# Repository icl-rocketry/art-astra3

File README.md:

# art-astra3
A repository for the third member in ART's ASTRA family

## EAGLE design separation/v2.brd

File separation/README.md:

# Separation

Hardware and software for a custom separation project

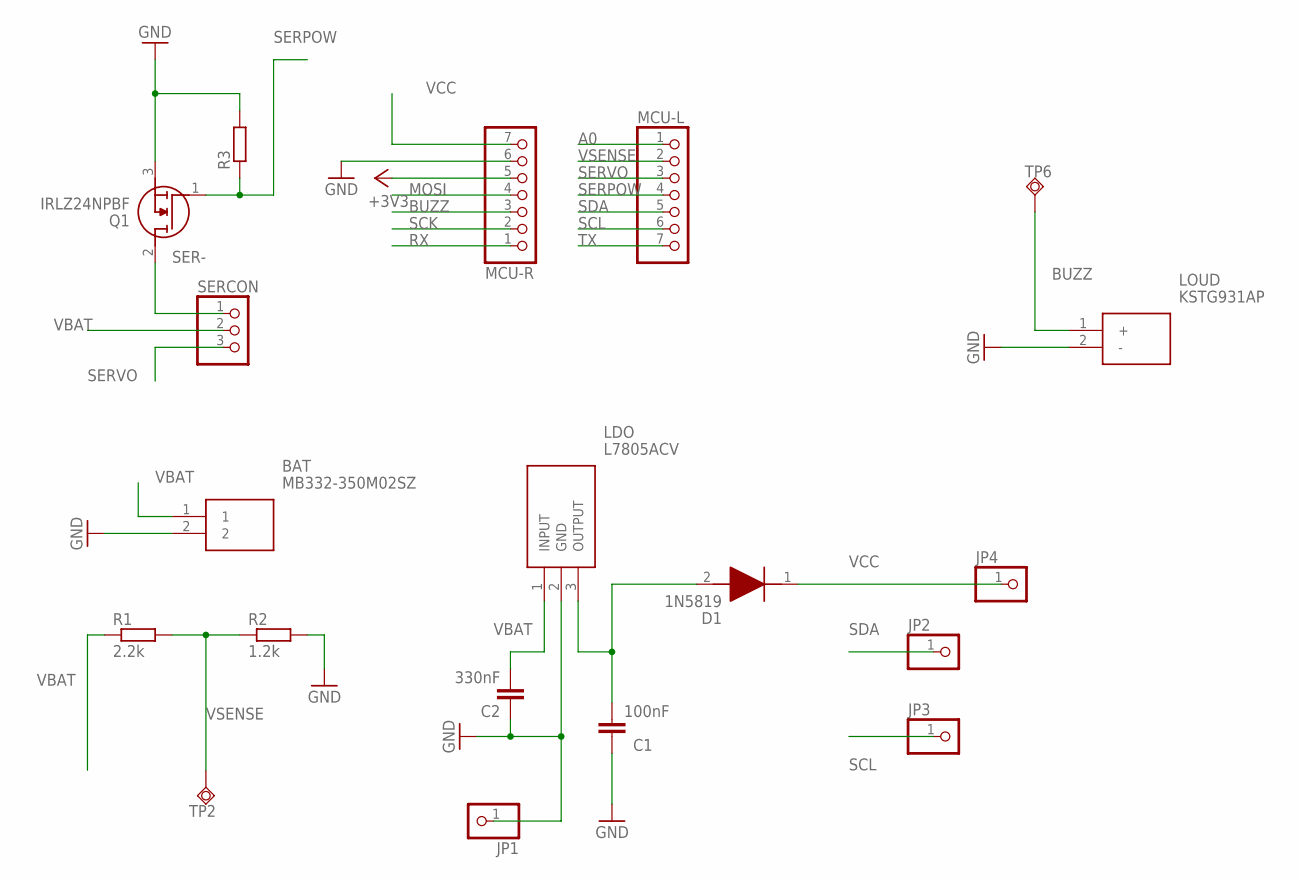
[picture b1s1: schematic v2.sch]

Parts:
BAT: MB332-350M02SZ; MB332350M02SZ
C1: 100nF; C025-024X044
C2: 330nF; C025-024X044
D1: 1N5819; DIOAD1414W86L464D238
JP1, JP2, JP3, JP4: PINHD-1X1; 1X01
LDO: L7805ACV; TO255P460X1020X2008-3P
LOUD: KSTG931AP; CAPPRD400W70D900H500
MCU-L: HEADER-1X7; 1X07_OVAL
MCU-R: HEADER-1X7; 1X07_OVAL
Q1: IRLZ24NPBF; TO254P469X1042X1967-3P
R1: 2.2k; 0204V
R2: 1.2k; 0204V
R3: R-EU_0204/2V; 0204V
SERCON: PINHD-1X3; 1X03
TP2, TP6: TPSQB2,54; B2,54

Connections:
+3V3: MCU-R.5
A0: MCU-L.1
BUZZ: LOUD.1 (+), MCU-R.3, TP6.TP
GND: BAT.2, C1.1, C2.1, JP1.1, LDO.2 (GND), LOUD.2 (-), MCU-R.6, Q1.3 (S), R2.2, R3.2
MOSI: MCU-R.4
RX: MCU-R.1
SCK: MCU-R.2
SCL: JP3.1, MCU-L.6
SDA: JP2.1, MCU-L.5
SER-: Q1.2 (D), SERCON.1
SERPOW: MCU-L.4, Q1.1 (G), R3.1
SERVO: MCU-L.3, SERCON.3
TX: MCU-L.7
VBAT: BAT.1, C2.2, LDO.1 (INPUT), R1.1, SERCON.2
VCC: D1.1 (K), JP4.1, MCU-R.7
VOUT: C1.2, D1.2 (A), LDO.3 (OUTPUT)
VSENSE: MCU-L.2, R1.2, R2.1, TP2.TP

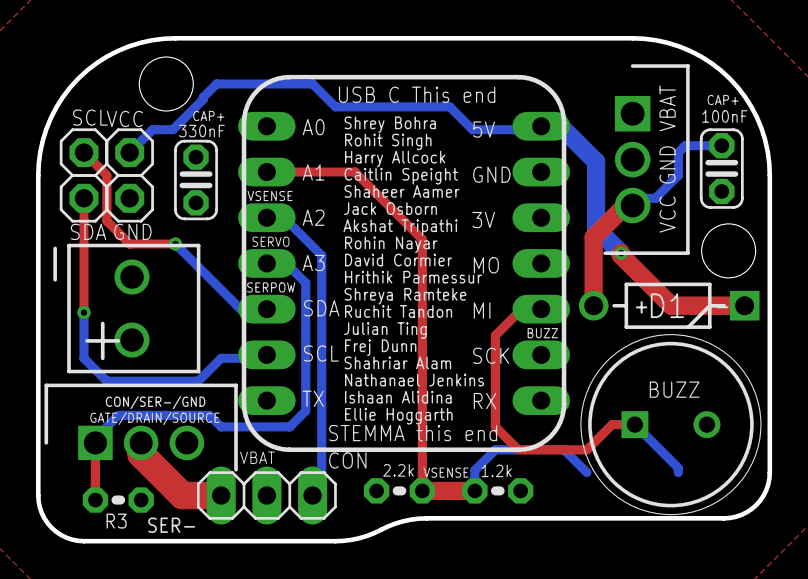
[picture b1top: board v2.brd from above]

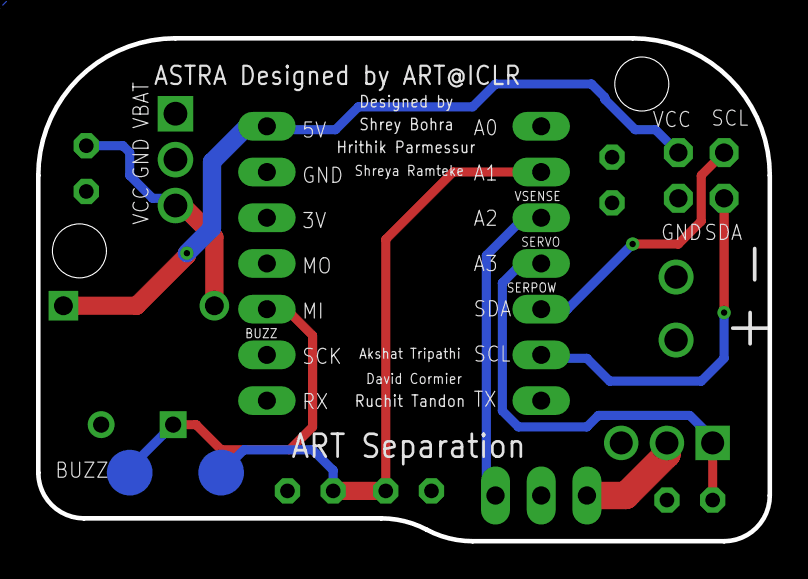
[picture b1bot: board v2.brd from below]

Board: 2 copper layers, 40.6 x 27.9 mm, 19 parts (2 on the bottom side), 11 nets.

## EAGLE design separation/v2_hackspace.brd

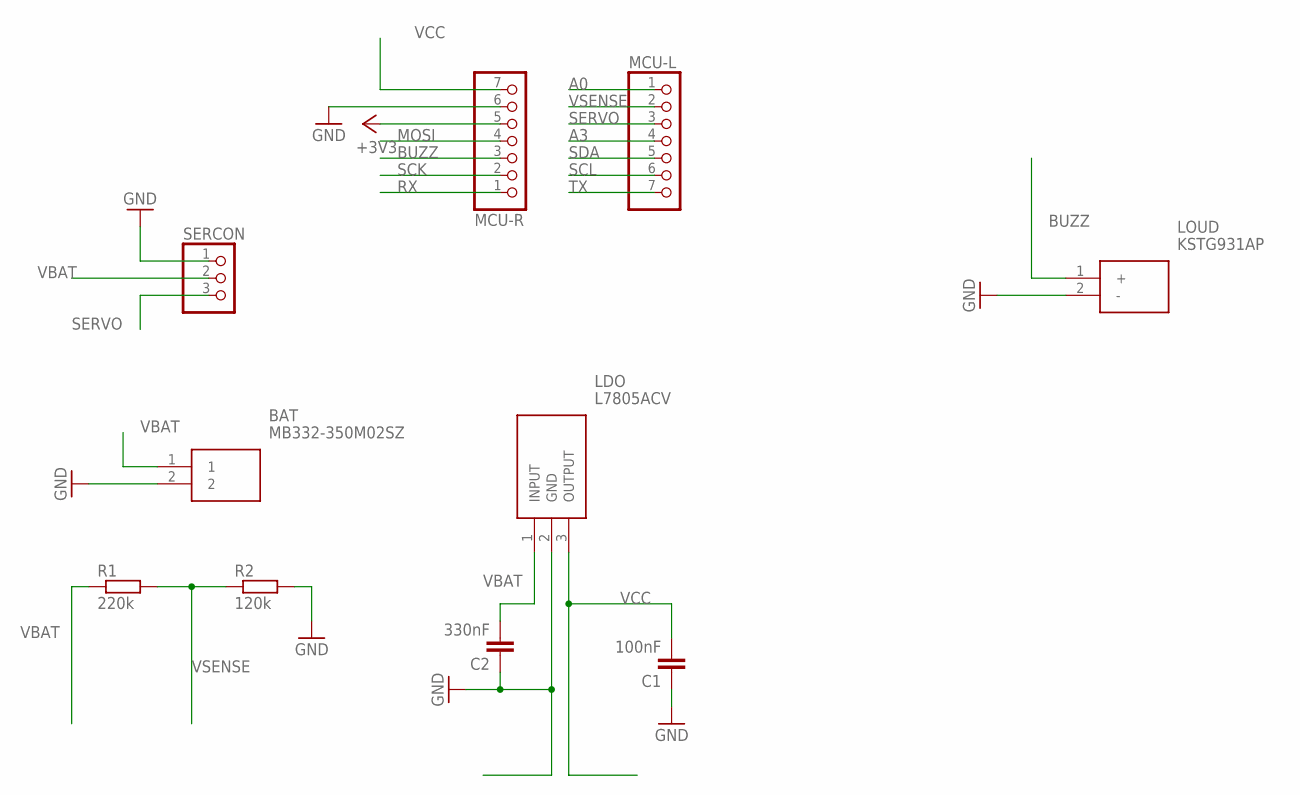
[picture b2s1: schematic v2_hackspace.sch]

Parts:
BAT: MB332-350M02SZ; MB332350M02SZ
C1: 100nF; C025-024X044
C2: 330nF; C025-024X044
LDO: L7805ACV; TO255P460X1020X2008-3P
LOUD: KSTG931AP; CAPPRD400W70D900H500
MCU-L: HEADER-1X7; 1X07_OVAL
MCU-R: HEADER-1X7; 1X07_OVAL
R1: 220k; 0204V
R2: 120k; 0204V
SERCON: PINHD-1X3; 1X03

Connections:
+3V3: MCU-R.5
A0: MCU-L.1
A3: MCU-L.4
BUZZ: LOUD.1 (+), MCU-R.3
GND: BAT.2, C1.1, C2.1, LDO.2 (GND), LOUD.2 (-), MCU-R.6, R2.2, SERCON.1
MOSI: MCU-R.4
RX: MCU-R.1
SCK: MCU-R.2
SCL: MCU-L.6
SDA: MCU-L.5
SERVO: MCU-L.3, SERCON.3
TX: MCU-L.7
VBAT: BAT.1, C2.2, LDO.1 (INPUT), R1.1, SERCON.2
VCC: C1.2, LDO.3 (OUTPUT), MCU-R.7
VSENSE: MCU-L.2, R1.2, R2.1

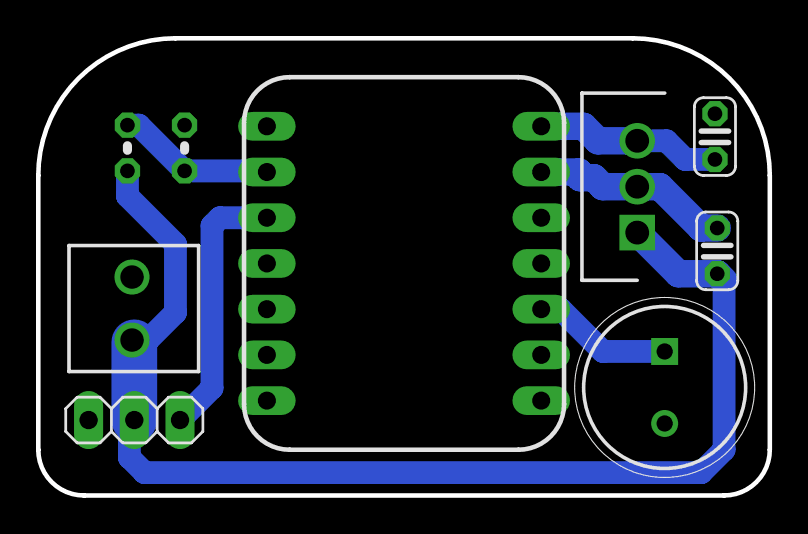
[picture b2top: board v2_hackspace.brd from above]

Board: 2 copper layers, 40.6 x 25.4 mm, 10 parts (0 on the bottom side), 6 nets.

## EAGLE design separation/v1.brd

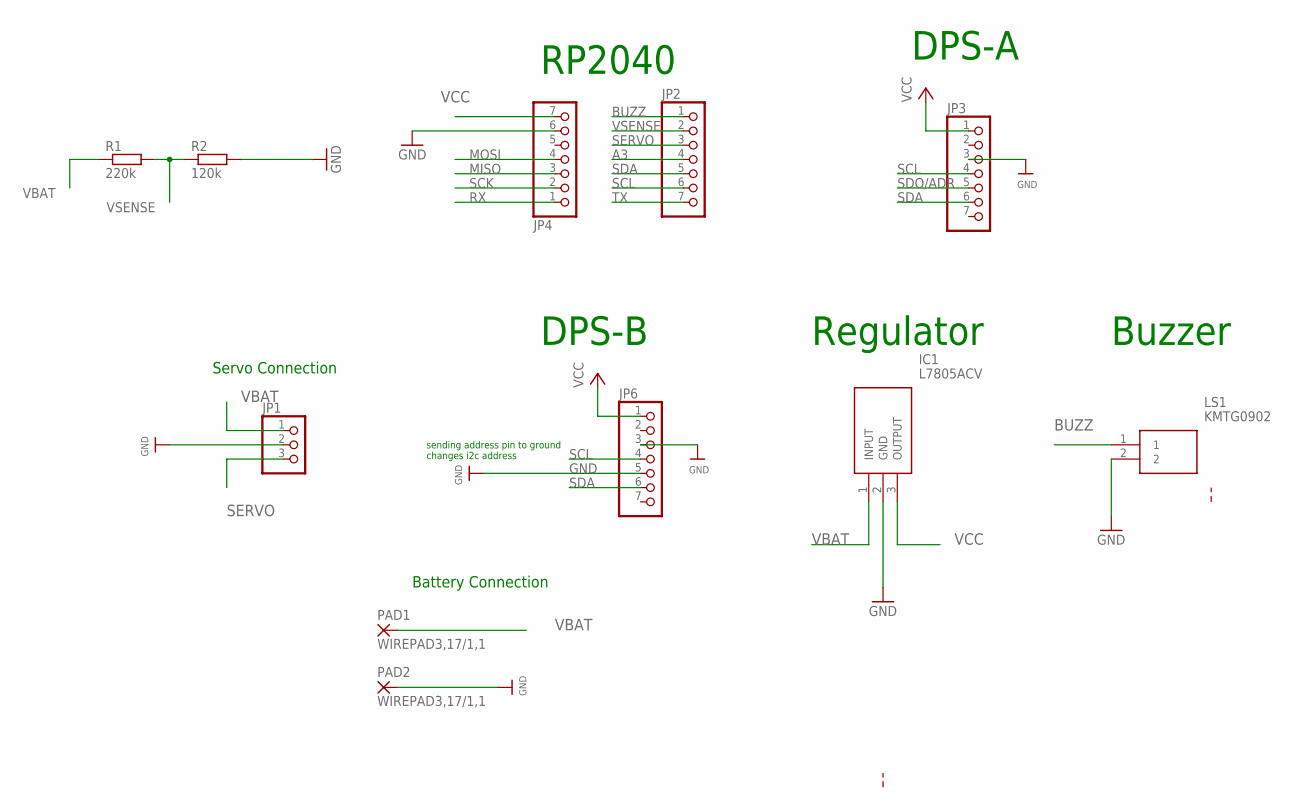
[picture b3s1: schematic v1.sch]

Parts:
IC1: L7805ACV; TO255P460X1020X2008-3P
JP1: PINHD-1X3; 1X03
JP2, JP4: HEADER-1X7; 1X07_OVAL
JP3, JP6: HEADER-1X770MIL; 1X07_ROUND_70
LS1: KMTG0902
PAD1, PAD2: WIREPAD3,17/1,1; 3,17/1,1
R1: 220k; 0204/5
R2: 120k; 0204/5

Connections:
A3: JP2.4
BUZZ: JP2.1, LS1.1
GND: IC1.2 (GND), JP1.2, JP3.3, JP4.6, JP6.3, JP6.5, LS1.2, PAD2.1, R2.2
MISO: JP4.3
MOSI: JP4.4
RX: JP4.1
SCK: JP4.2
SCL: JP2.6, JP3.4, JP6.4
SDA: JP2.5, JP3.6, JP6.6
SDO/ADR: JP3.5
SERVO: JP1.3, JP2.3
TX: JP2.7
VBAT: IC1.1 (INPUT), JP1.1, PAD1.1, R1.1
VCC: IC1.3 (OUTPUT), JP3.1, JP4.7, JP6.1
VSENSE: JP2.2, R1.2, R2.1

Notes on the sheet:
RP2040
DPS-A
DPS-B
Regulator
Buzzer
Servo Connection
Battery Connection
sending address pin to ground changes i2c address

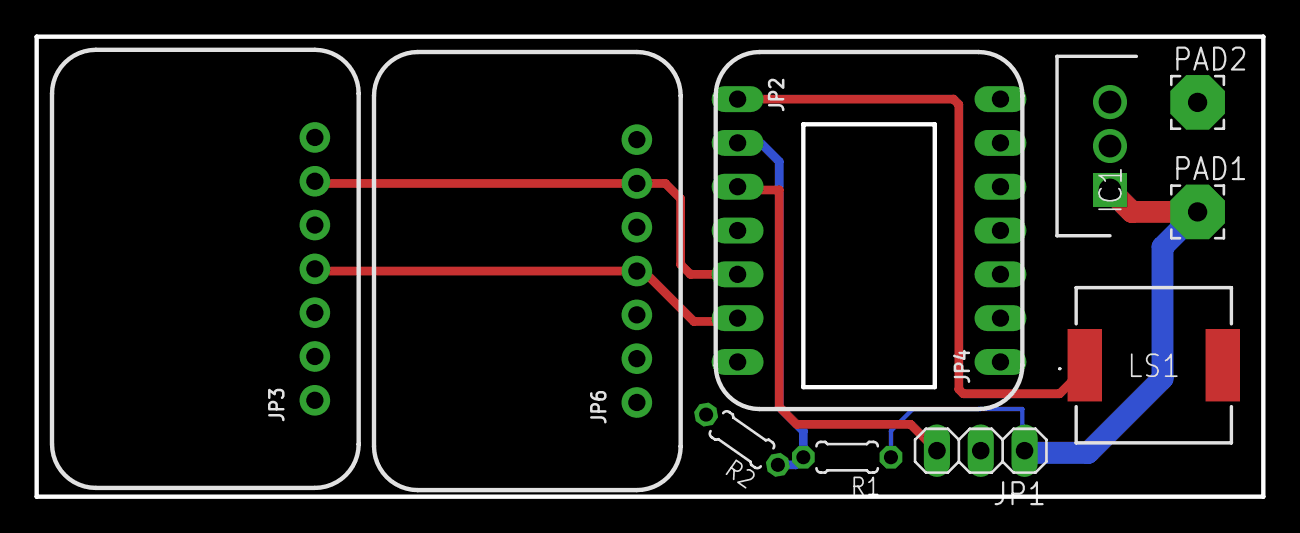
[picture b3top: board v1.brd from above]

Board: 2 copper layers, 71.1 x 26.7 mm, 11 parts (0 on the bottom side), 8 nets.

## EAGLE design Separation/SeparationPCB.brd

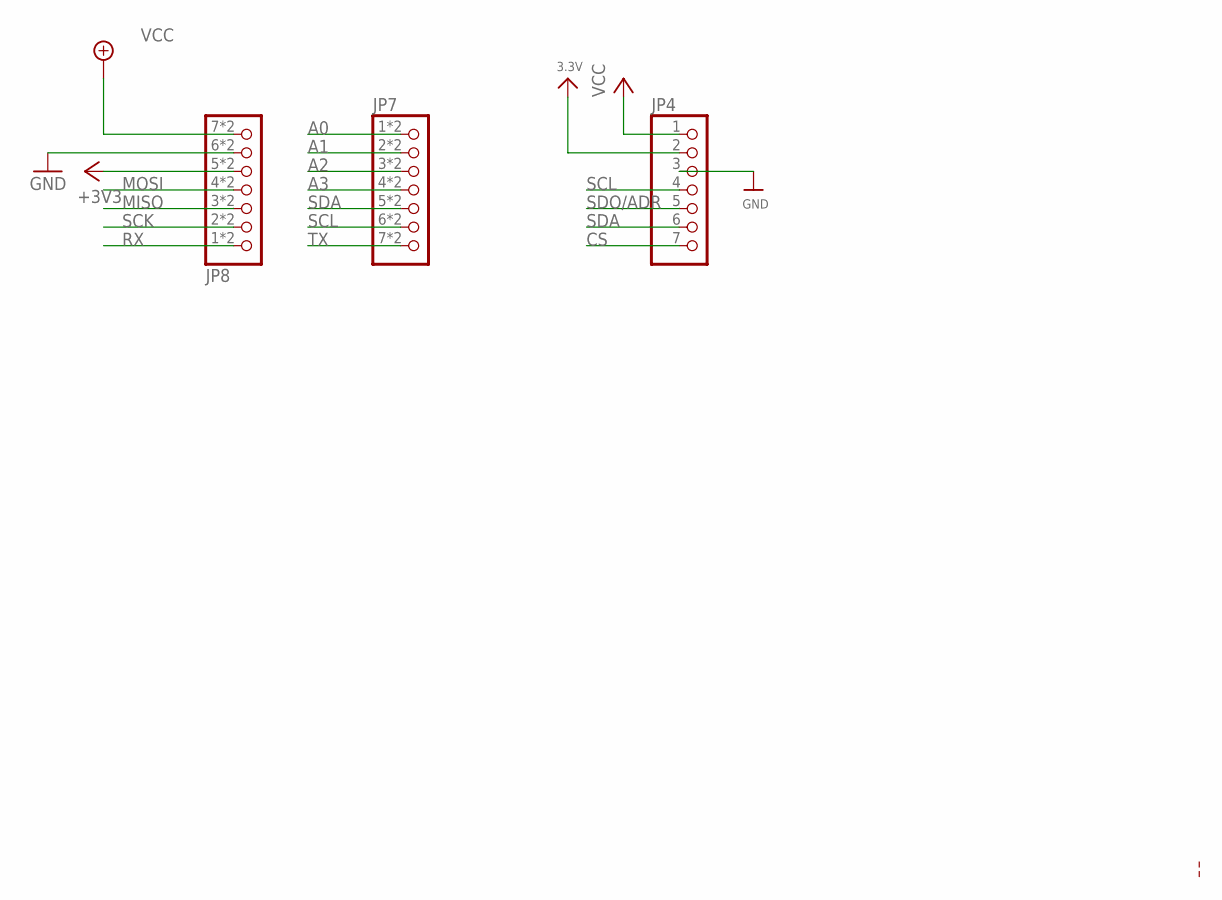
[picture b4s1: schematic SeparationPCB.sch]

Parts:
JP4: HEADER-1X770MIL; 1X07_ROUND_70
JP7, JP8: HEADER-1X7_CASTEL; 1X07_CASTEL

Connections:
3.3V: JP4.2
+3V3: JP8.5, JP8.5C (5)
A0: JP7.1, JP7.1C (1)
A1: JP7.2, JP7.2C (2)
A2: JP7.3, JP7.3C (3)
A3: JP7.4, JP7.4C (4)
CS: JP4.7
GND: JP4.3, JP8.6, JP8.6C (6)
MISO: JP8.3, JP8.3C (3)
MOSI: JP8.4, JP8.4C (4)
RX: JP8.1, JP8.1C (1)
SCK: JP8.2, JP8.2C (2)
SCL: JP4.4, JP7.6, JP7.6C (6)
SDA: JP4.6, JP7.5, JP7.5C (5)
SDO/ADR: JP4.5
TX: JP7.7, JP7.7C (7)
VCC: JP4.1, JP8.7, JP8.7C (7)

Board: 2 copper layers, 3 parts (0 on the bottom side), 14 nets, no tracks yet.

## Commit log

2022-01-22 We just got python started.
2022-01-22 Just started using github.
2022-01-22 create altitude function
2022-01-22 averaging pseudocode
2022-02-15 Separation Initial Schematic
2022-02-22 add design blocks
2022-02-22 sparkfun eagle setup script
2022-02-22 aisler design rules
2022-02-22 increase length of castellated pad
2022-02-22 move dim layer to tplace
2022-02-22 rename +5V to VCC
2022-02-23 Create SamacSys_Parts.lbr
    components from rs
2022-02-23 create new separation project
2022-02-23 add L7805ACV voltage regulator to library
2022-02-23 create blank schematic and board
2022-02-23 add rp2040
2022-02-23 remove +5v connector
2022-02-23 add 2x dps
2022-02-23 add regulator
2022-02-23 add buzzer
2022-02-23 add servo connection
2022-02-23 basic board layout
2022-02-23 remove all 3v3 lines
2022-02-23 remove cs lines
2022-02-23 create dimension
2022-02-23 create gnd plane on top layer
2022-02-23 create vcc plane on bottom layer
2022-02-23 ratsnest
2022-02-23 move keepout to correct pos
2022-02-23 tweak rp2040 tstop
2022-02-23 flip servo connector for better routing
2022-02-23 rename to v1
2022-02-23 add buzzers to rs lib
2022-02-23 add 3d models
2022-02-23 update boards to use 3d packages
2022-02-24 add voltage divider
2022-02-24 connect resistors
2022-02-24 reconfigure lower section
2022-02-24 redraw outside dimension
2022-02-24 move r2 away from edge
2022-02-24 add central cutout
2022-03-01 started v2 board
2022-03-12 Moved hardware to hw folder
2022-03-12 Added filter and trigger classes
2022-03-13 tweak tStop
2022-03-13 move hardware files up one level
    EAGLE didn't like its folder structure being changed
2022-03-13 initialise new v2 board
2022-03-16 add rocket internal dim
2022-03-16 add mcu
2022-03-16 9mm buzzer
2022-03-16 add support components
2022-03-16 rename components to be helpful
2022-03-16 servo connection
2022-03-16 ground components
2022-03-16 connect components to nets
2022-03-16 add potential divider
2022-03-16 fix top left tstop alignment
2022-03-16 connect comps to pins
2022-03-16 initial layout
2022-03-16 replace resistor footprint with smaller version
2022-03-16 optimise placement
2022-03-16 reorder IO pins
2022-03-16 remove unnecessary labels
2022-03-16 routed
2022-03-16 create a copy to physically place components
2022-03-16 add 3x pressure sensors to physical model
2022-03-16 possible physical layout
2022-03-17 shuffle right group down
2022-03-17 draw intiial outline
2022-03-17 move buzzer PWM out to MISO pin
2022-03-17 make corners symmetrical
2022-03-17 rotate regulator
2022-03-17 connect buzz
2022-03-17 pours
2022-03-17 remove reference diameter
2022-03-17 central cutout for flush smd
2022-03-18 add 2x 3mm mounting holes
2022-03-18 move to place centre of bottom edge at origin
2022-03-18 increase thickness of section connections
2022-03-18 align mounting holes
2022-03-18 reshuffle board to have stemma qt pointing inwards
2022-03-18 label dims
    40.64 x 25.40 mm (not inc rounded corners)
2022-03-21 remove central cutout - not manufacturable
2022-03-21 swap term blocks and resistors
2022-03-21 swap vsense and servo pins on mcu
2022-03-21 change servo connector pinout to match flight servo
    MG2611WHV
2022-03-21 extend mcu smt pads
2022-03-21 label mcu pins
2022-03-21 add test points for signals with no easy access
2022-03-21 add headers to use second i2c bus if required
2022-03-21 add ICLR logo
2022-03-21 labels; move vcc to top
2022-03-21 labels
2022-03-21 names
2022-03-21 del tp labels
2022-03-21 fix vcc not connected
2022-03-21 apply aisler drc
2022-03-21 add 2x caps for regulator
2022-03-21 place caps
2022-03-21 complete DRC and labelling
2022-03-21 forgot a name oops
2022-03-21 embiggen pads, final drc
2022-03-21 update physical map with updated board
2022-03-22 create a copy to be manufactured at hackspace
2022-03-22 remove nice labels
2022-03-22 ripup all signals
2022-03-22 remove testpoints
2022-03-22 remove mounting hole
2022-03-22 easy traces
2022-03-22 remove spare breakouts
2022-03-22 complete reconnecting
2022-03-22 remove extra tstop
2022-03-23 complete hackspace pcb
2022-03-23 swap top and bottom labels for better legibility
2022-03-26 Added statemachine skeleton
2022-03-26 Added code.py
2022-03-27 Added trajectory generation code
2022-03-27 Added test method
2022-03-27 Added main function to separation tester
2022-03-28 Minor changes to gitignore
2022-03-28 Switched to median filtering
2022-03-28 Split data into 2 easier to analyse files
2022-03-28 Added dataset where astra is at rest
2022-03-28 Updated trigger to use combos
2022-03-28 Added csv plotter tool
2022-03-28 Added test cases
2022-03-28 Updated csv plotter to use EOF
2022-03-28 Added more test cases
2022-03-28 Added pressure threshold to trigger
2022-03-29 Added basic video recording
2022-03-29 Added gpio based stopping
2022-03-30 Added pressure chamber readings
2022-04-02 Added Makefile for easy remote development
2022-04-02 Removed dead code
2022-04-02 Updated median filter to use custom ring buffer since deque isn't in circuitpython
2022-04-02 Added boot.py
2022-04-02 Updated trigger to take in data
2022-04-02 Fleshed out statemachine
2022-04-02 Minor stuff really
2022-04-02 Moved tsv files to test_data directory
2022-04-02 Updated separation_sim to work with new changes
2022-04-02 Fixed infinite loop bug
2022-04-02 Added static type checking with mypy
2022-04-02 Fixed Makefile and set default target to copy
2022-04-02 Hopefilly fixed bugs in statemachine
2022-04-03 Updated code to use pass static checking
2022-04-03 Updated python typing version to 3.10
2022-05-14 add schottky to lib
2022-05-14 add Infineon IRLZ24NPBF to samacsys lib
2022-05-14 connect mosfet in schematic
2022-05-14 fix mosfet connections
2022-05-14 remake outline
2022-05-14 remake pours
2022-05-14 complete mosfet integration
2022-05-14 increase pour isolate
    now 0.01
2022-05-14 drc check
2022-05-14 consistent orientation for caps
2022-05-14 remove extra solder pad area
2022-05-15 add diode on regulator output
2022-05-15 wire in diode
2022-05-15 push to fusion
2022-05-20 move decoupling cap closer to regulator
2022-05-20 shift trace to enable ground pour over logo
2022-05-21 Added stress tester
2022-07-07 define pins
2022-07-07 set mosfet pin as digital IO
2022-07-07 setup servo pwm output
2022-07-07 create move loop
2022-07-07 idk python weird
2022-07-07 // divide
2022-07-07 apex speaker lib
2022-07-07 buzzer feedback
2022-07-07 validate input range
2022-07-07 also validate input line
2022-07-07 improve feedback
2023-02-25 removed stuff
2023-03-07 fix voltage divider vals

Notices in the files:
parts and their libraries:
microbuilder: This work is placed in the public domain, and may be freely used for commercial and non-commercial work with the following conditions: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
